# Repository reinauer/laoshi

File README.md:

# Project Laoshi (老師)

This is a simple ROM bank switcher for certain Amiga ROMs that allows switching between two ROM banks through reads from the host side.

There are three versions for your heart's delight: An SMD version, a through hole version, and a flat version to fit in space limited devices like the A590:

## Through Hole

## SMD

## A590

# Implementation / BOM

Gerbers will be in each subdirectory under hardware. An ATF16V8 is needed
(either through hole or TSSOP) and should be programmed with laoshi.pld which
can be found under logic/

During assembly you need to cut pins 1 and 27 of the ROM socket.

When assembling the A590 version, don't use a socket for the flash chip. It is
also recommended to cut the pins of the pin headers flat to the PCB surface
before soldering, and covering the top with kapton tape to prevent shorts.

# Example pictures

## Through Hole version

## A590 version

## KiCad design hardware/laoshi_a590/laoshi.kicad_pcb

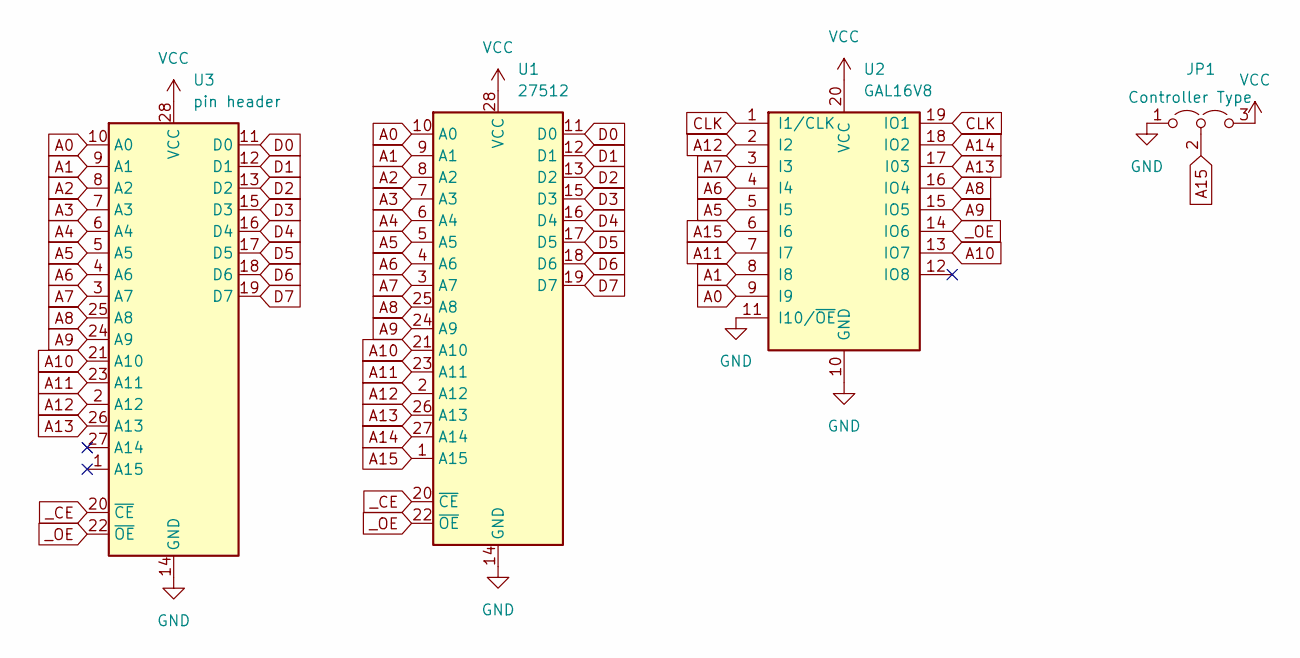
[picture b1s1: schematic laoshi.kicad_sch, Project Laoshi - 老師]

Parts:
JP1: Controller Type; SolderJumper-3_P1.3mm_Open_RoundedPad1.0x1.5mm_NumberLabels
U1: 27512; DIP-28_W15.24mm_LongPads
U2: GAL16V8; TSSOP-20_4.4x6.5mm_P0.65mm
U3: pin header; DIP-28_W15.24mm_LongPads

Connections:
A0: U1.10 (A0), U2.9 (I9), U3.10 (A0)
A1: U1.9 (A1), U2.8 (I8), U3.9 (A1)
A2: U1.8 (A2), U3.8 (A2)
A3: U1.7 (A3), U3.7 (A3)
A4: U1.6 (A4), U3.6 (A4)
A5: U1.5 (A5), U2.5 (I5), U3.5 (A5)
A6: U1.4 (A6), U2.4 (I4), U3.4 (A6)
A7: U1.3 (A7), U2.3 (I3), U3.3 (A7)
A8: U1.25 (A8), U2.16 (IO4), U3.25 (A8)
A9: U1.24 (A9), U2.15 (IO5), U3.24 (A9)
A10: U1.21 (A10), U2.13 (IO7), U3.21 (A10)
A11: U1.23 (A11), U2.7 (I7), U3.23 (A11)
A12: U1.2 (A12), U2.2 (I2), U3.2 (A12)
A13: U1.26 (A13), U2.17 (I03), U3.26 (A13)
A14: U1.27 (A14), U2.18 (IO2)
A15: JP1.2 (C), U1.1 (A15), U2.6 (I6)
CLK: U2.1 (I1/CLK), U2.19 (IO1)
D0: U1.11 (D0), U3.11 (D0)
D1: U1.12 (D1), U3.12 (D1)
D2: U1.13 (D2), U3.13 (D2)
D3: U1.15 (D3), U3.15 (D3)
D4: U1.16 (D4), U3.16 (D4)
D5: U1.17 (D5), U3.17 (D5)
D6: U1.18 (D6), U3.18 (D6)
D7: U1.19 (D7), U3.19 (D7)
GND: JP1.1 (A), U1.14 (GND), U2.10 (GND), U2.11 (I10/~OE), U3.14 (GND)
VCC: JP1.3 (B), U1.28 (VCC), U2.20 (VCC), U3.28 (VCC)
_CE: U1.20 (~CE), U3.20 (~CE)
_OE: U1.22 (~OE), U2.14 (IO6), U3.22 (~OE)

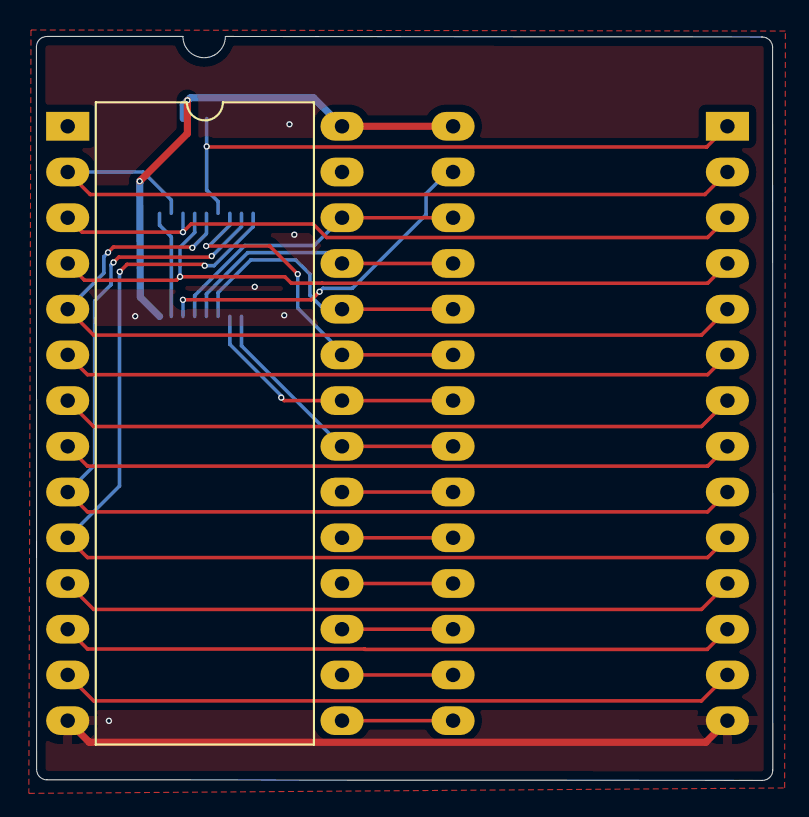
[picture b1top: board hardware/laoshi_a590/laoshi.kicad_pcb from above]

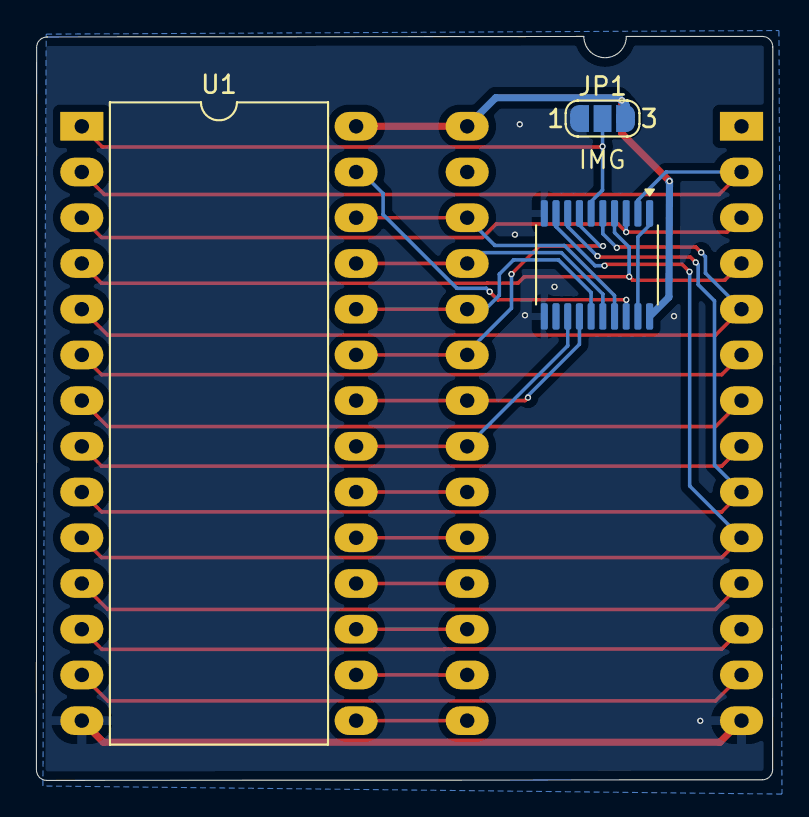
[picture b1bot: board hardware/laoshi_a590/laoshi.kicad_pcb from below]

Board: 2 copper layers, 40.9 x 41.3 mm, 4 parts (3 on the bottom side), 29 nets.

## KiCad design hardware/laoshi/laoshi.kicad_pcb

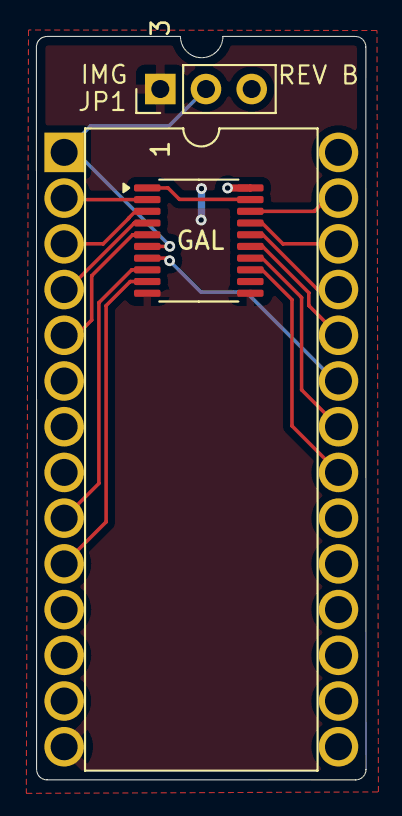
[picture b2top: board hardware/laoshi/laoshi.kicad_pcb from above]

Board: 2 copper layers, 18.3 x 41.3 mm, 3 parts (0 on the bottom side), 17 nets.

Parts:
JP1: Image; PinHeader_1x03_P2.54mm_Vertical
U1: 27512; DIP-28_W15.24mm
U2: GAL16V8; TSSOP-20_4.4x6.5mm_P0.65mm

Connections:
A0: U1.10 (A0), U2.9 (I9)
A1: U1.9 (A1), U2.8 (I8)
A5: U1.5 (A5), U2.5 (I5)
A6: U1.4 (A6), U2.4 (I4)
A7: U1.3 (A7), U2.3 (I3)
A8: U1.25 (A8), U2.16 (IO4)
A9: U1.24 (A9), U2.15 (IO5)
A10: U1.21 (A10), U2.13 (IO7)
A11: U1.23 (A11), U2.7 (I7)
A12: U1.2 (A12), U2.2 (I2)
A13: U1.26 (A13), U2.17 (I03)
A14: U1.27 (A14), U2.18 (IO2)
A15: JP1.2 (C), U1.1 (A15), U2.6 (I6)
CLK: U2.1 (I1/CLK), U2.19 (IO1)
GND: JP1.1 (A), U1.14 (GND), U2.10 (GND), U2.11 (I10/~OE)
VCC: JP1.3 (B), U1.28 (VCC), U2.20 (VCC)
_OE: U1.22 (~OE), U2.14 (IO6)

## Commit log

2024-06-03 Initial logic
2024-06-03 Add Through Hole version of Laoshi
2024-06-03 Add SMD version of Laoshi
2024-06-03 Add README.md
2024-06-11 Add test script for the laoshi logic
2024-06-12 logic: Detect serial port in tests
    - factor out brutus28 specific code into brutus28.tcl
    - add code to detect serial port on MacOS and Linux
2024-06-12 brutus28.tcl: Fix comment
2024-06-12 logic: Add Chris Hooper's term utility
2024-10-13 Add a super low footprint version
2024-10-13 Massage README
2024-10-13 Show pictures next to each other
2024-10-13 Move SMD version pictures next to each other
2024-10-13 Add A590 version to README
2024-10-13 Add pictures of assembled PCBs
2024-10-13 Add gerbers for a590 version
2024-10-14 Gerbers for TH version
2026-01-20 PLD: Simplify code
